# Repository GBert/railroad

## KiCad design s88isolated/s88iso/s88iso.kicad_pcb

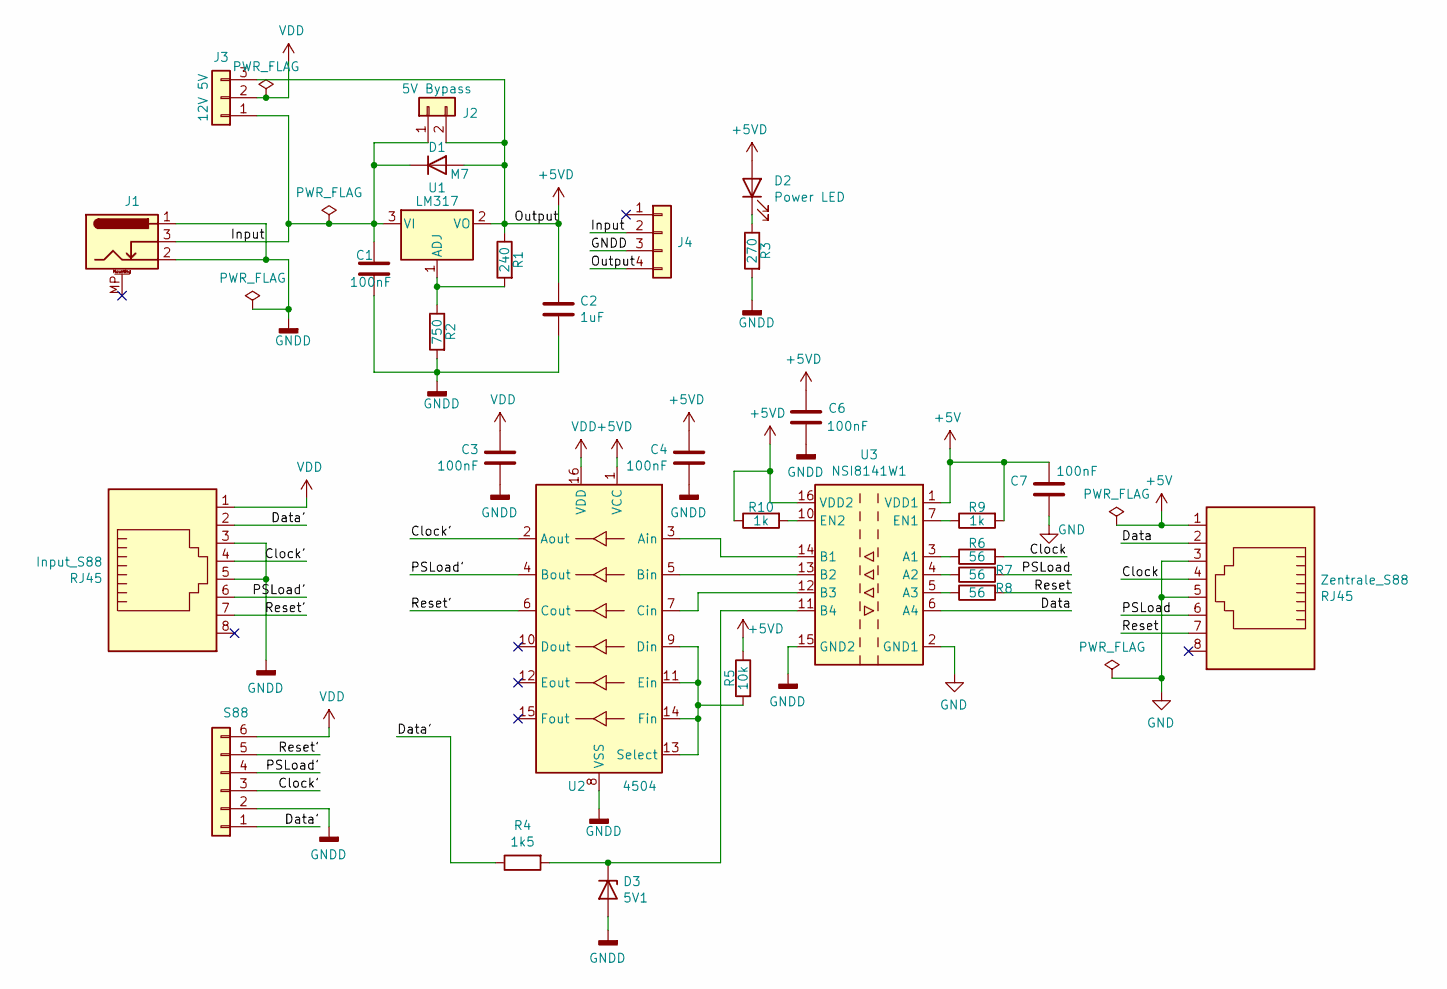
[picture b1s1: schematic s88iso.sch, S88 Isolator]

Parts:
C1, C3, C4, C6, C7: 100nF; C_0805_2012Metric; LCSC C28233
C2: 1uF; C_0805_2012Metric_Pad1.18x1.45mm_HandSolder; LCSC C28323
D1: M7; D_SMA; LCSC C95872
D2: Power LED; LED_0603_1608Metric_Pad1.05x0.95mm_HandSolder; LCSC C72043
D3: 5V1; D_0805_2012Metric_Pad1.15x1.40mm_HandSolder
Input_S88: RJ45; megb8-8-Uni
J1: Barrel_Jack_Switch_MountingPin; dc_socket
J2: 5V Bypass; PinHeader_1x02_P2.54mm_Vertical
J3: 12V 5V; PinHeader_1x03_P2.54mm_Vertical
J4: Conn_01x04; PinSocket_1x04_P2.54mm_Vertical
R1: 240; R_0603_1608Metric_Pad0.98x0.95mm_HandSolder; LCSC C23350
R2: 750; R_0603_1608Metric_Pad0.98x0.95mm_HandSolder; LCSC C23241
R3: 270; R_0603_1608Metric_Pad0.98x0.95mm_HandSolder; LCSC C22966
R4: 1k5; R_0805_2012Metric; LCSC C4310
R5: 10k; R_0805_2012Metric; LCSC C25804
R6, R7, R8: 56; R_0603_1608Metric_Pad0.98x0.95mm_HandSolder; LCSC C25196
R9, R10: 1k; R_0603_1608Metric_Pad0.98x0.95mm_HandSolder; LCSC C21190
S88: Conn_01x06; PinSocket_1x06_P2.54mm_Horizontal
U1: LM317; TO-252-2; LCSC C75510
U2: 4504; SOIC-16_3.9x9.9mm_P1.27mm; LCSC C151885
U3: NSI8141W1; SOIC-16W_7.5x10.3mm_P1.27mm; LCSC C399514
Zentrale_S88: RJ45; megb8-8-Uni

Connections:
+5V: C7.1, R9.2, U3.1 (VDD1), Zentrale_S88.1
/Clock: R6.2, Zentrale_S88.4
/Clock': Input_S88.4, S88.3, U2.2 (Aout)
/Data: U3.6 (A4), Zentrale_S88.2
/Data': Input_S88.2, R4.1, S88.1
/Input: C1.1, D1.1 (K), J1.3, J2.1, J3.1, J4.2, U1.3 (VI)
/PSLoad: R7.2, Zentrale_S88.6
/PSLoad': Input_S88.6, S88.4, U2.4 (Bout)
/Reset: R8.2, Zentrale_S88.7
/Reset': Input_S88.7, S88.5, U2.6 (Cout)
GND: C7.2, U3.2 (GND1), U3.8 (GND1), Zentrale_S88.3, Zentrale_S88.5
GNDD: C1.2, C2.2, C3.2, C4.2, C6.2, D3.2 (A), Input_S88.3, Input_S88.5, J1.1, J1.2, J4.3, R2.2, R3.2, S88.2, U2.8 (VSS), U3.9 (GND2), U3.15 (GND2)
unnamed: D2.1 (K), R3.1
unnamed: D3.1 (K), R4.2, U3.11 (B4)
unnamed: R1.2, R2.1, U1.1 (ADJ)
unnamed: U2.3 (Ain), U3.14 (B1)
unnamed: U2.5 (Bin), U3.13 (B2)
unnamed: U2.7 (Cin), U3.12 (B3)
unnamed: R5.2, U2.9 (Din), U2.11 (Ein), U2.13 (Select), U2.14 (Fin)
unnamed: R6.1, U3.3 (A1)
unnamed: R7.1, U3.4 (A2)
unnamed: R8.1, U3.5 (A3)
unnamed: R9.1, U3.7 (EN1)
unnamed: R10.2, U3.10 (EN2)
VDD: C3.1, Input_S88.1, J3.2, S88.6, U2.16 (VDD)

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
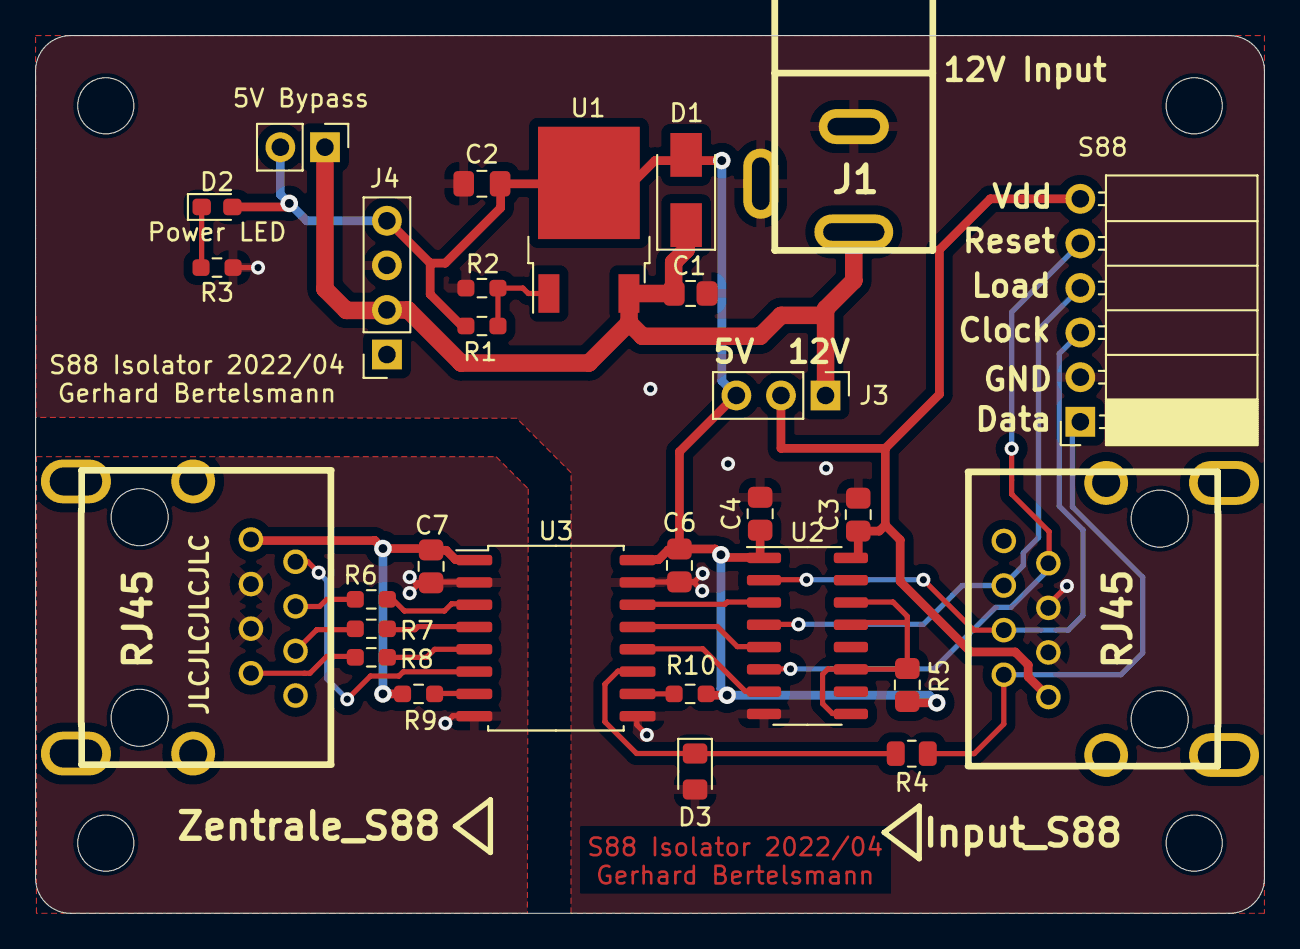
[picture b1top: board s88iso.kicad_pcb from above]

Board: 2 copper layers, 70.0 x 50.0 mm, 29 parts (0 on the bottom side), 27 nets.

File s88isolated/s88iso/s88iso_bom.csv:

Comment,Designator,Footprint,LCSC
"1uF","C2","Capacitor_SMD:C_0805_2012Metric_Pad1.18x1.45mm_HandSolder","C28323"
"100nF","C1,C3,C4,C6,C7","Capacitor_SMD:C_0805_2012Metric","C28233"
"M7","D1","Diode_SMD:D_SMA","C95872"
"Power LED","D2","LED_SMD:LED_0603_1608Metric_Pad1.05x0.95mm_HandSolder","C72043"
"240","R1","Resistor_SMD:R_0603_1608Metric_Pad0.98x0.95mm_HandSolder","C23350"
"750","R2","Resistor_SMD:R_0603_1608Metric_Pad0.98x0.95mm_HandSolder","C23241"
"270","R3","Resistor_SMD:R_0603_1608Metric_Pad0.98x0.95mm_HandSolder","C22966"
"1k5","R4","Resistor_SMD:R_0805_2012Metric","C4310"
"10k","R5","Resistor_SMD:R_0805_2012Metric","C25804"
"56","R6,R7,R8","Resistor_SMD:R_0603_1608Metric_Pad0.98x0.95mm_HandSolder","C25196"
"1k","R9,R10","Resistor_SMD:R_0603_1608Metric_Pad0.98x0.95mm_HandSolder","C21190"
"LM317","U1","Package_TO_SOT_SMD:TO-252-2","C75510"
"4504","U2","Package_SO:SOIC-16_3.9x9.9mm_P1.27mm","C151885"
"NSI8141W1","U3","Package_SO:SOIC-16W_7.5x10.3mm_P1.27mm","C399514"

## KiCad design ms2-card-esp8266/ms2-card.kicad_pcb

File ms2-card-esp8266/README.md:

Lokkarten Emulator
==================

Auf der Lokkarte befindet sich ein I2C EEPROM (24LC64 64kBit -> 8kByte). Die Schaltung
ersetzt den Speicher durch ein kompatiblen FRAM Baustein (U2). Dadurch entfällt die
zeitkritische I2C Slave Behandlung.

Der Prozessor (ESP8266 oder extern) befüllt den FRAM Baustein mit Lokkarten Daten. Damit
es zu keinen Komplikationen auf dem MS2 I2C Bus kommen kann, ist der I2C Bus durch analoge
Schalter (BL1551B - Signal I2C_Select) getrennt.

Der Prozessor signalisiert das Einstecken der Lokkarte (Signal Card) durch Verbindung
der Kontakte am Kartenrand.

Die Platine wurde mit KiCad 7.0.11 erstellt. Die Produktionsdaten wurden mit dem JLCPCB
Fabrication Toolkit Plugin generiert (Verzeichnis production). Platinendicke: 0,8 mm wählen !

Die zwei Fehler im DRC Check (Corteyards overlap) können ignoriert werden, da die Bestückung
mit dem SPI EEPROM U10 und C11 alternativ ist.

Detail-Beschreibung
-------------------

Der Kartenwechsel wird bei der MS2 über einen mechanischen Taster erkannt. Bei der MS2 wurden
verschiedene Arten des Tasters verbaut. Die Platine verwendet einen federnden Testpin, damit
ein Kartenwechsel für die verschiedene Bauarten simuliert werden kann:
https://dirtypcbs.com/store/designer/details/ian/12/dirty-pogo-pins

Power Select: hier wählt man zwiechen Versorgung durch MS2 oder USB.

Schaltregler kann als Ersatz dienen, wenn der Längsregler U6 nicht ausreicht.
Dazu muss U6 aber entfernt werden.

Für C1 ist ein Tantal Kondensator vorgesehen. Da Tantal aber ein Rohstoff aus Krisengebieten
ist, ist ein anderer Kondensator mit niedrigem ESR ratsam. Die Pads sollten genügend Platz bieten,
einen anderen Kondensator einzusetzen, wie z.B. Reichelts "VF 100/6,3 P-C" oder "VF 100/16 P-D".

Silabs CP2102 wurde für die Seriell-USB Anbindung gewählt, weil dieser ein guter Kompromiss
zwischen Stabilität, Unterstützung und Preis ist.

Q1/Q2 und R8/R9 dienen dazu, das Update der ESP8266 ohne Eingriff zu ermöglichen.

U3 und U4 trennen den I2C Bus von der MS2, damit es keine Störungen des MS2 I2C-Busses gibt.
I2C Select schaltet entweder den ESP8266 oder alternativ einen anderen I2C Master
für den Zugriff auf das FRAM hinzu.

U20 dient dazu, einen Kartenwechsel der MS2 zu signalisieren.

Das MS2 I2C Bus Clock Signal wird zusätzlich auch noch über Q1 und ein RC Glied an den ADC
des ESP8266 Moduls angeschlossen, um den Zeitpunkt des letzten I2C Bus Zugriffs zu messen.

TODOs/Done
----------

- CP2102 Test  - OK
- I2C intern Test - OK
- I2C extern Test - OK
- ESP Programmierung Test - OK
- SD Kartenanbindung Test - OK
- Allternative zur SD-Karte - SPI EEPROM - ungetestet

Hardware / neue Version
- 470 nH Vdd

ESP8266 - Code Segmente
-----------------------

```
#define SPI_MISO    12
#define SPI_MOSI    13
#define SPI_CLK     14
#define SPI_CS      15

#define I2C_Select   2
#define I2C_SDA      4
#define I2C_SCL      5
#define Card_Change 16

void setup () {
  // SD Karte initialisieren
  SD.begin(SPI_CS)

  // I2C initilisieren
  Wire.begin(I2C_SDA, I2C_SCL);
  Wire.setClock(100000);

  pinMode(Card_Change, OUTPUT);
  pinMode(I2C_Select, OUTPUT);
}

  // MS2 I2C FRAM Zugriff
  digitalWrite(I2C_Select, 0);
  ...
  // ESP8266 I2C FRAM Zugriff
  digitalWrite(I2C_Select, 1);

  // Kartenwechsel emulieren
  digitalWrite(Card_Change, 0)
  delay(500);
  digitalWrite(Card_Change, 1)

```

Flashing
--------
```
esptool.py --port /dev/ttyUSB1 erase_flash
esptool.py --port /dev/ttyUSB1 --baud 460800 write_flash --flash_size=detect 0 ./build_output/firmware/tasmota.bin
```

OLD - BACKUP
------------

SD-CARD
-------
https://github.com/arendst/Tasmota/discussions/13938

https://www.mikrocontroller.net/articles/MMC-_und_SD-Karten

Raspberry Pi I2C
----------------

|Function  | GPIO   | Pin    |      |
|----------|--------|--------|------|
|SDA       | GPIO2  | Pin 3  |      |
|SCL       | GPIO3  | Pin 5  |      |

Tasmota Tests
-------------

git clone https://github.com/arendst/Tasmota.git
cd Tasmota
git tag
pio run

{"NAME":"ESP-12F","GPIO":[1,1,1,1,1,1,0,0,1,1,1,1,1,1],"FLAG":0,"BASE":18}

user_config_override.h
```
// Select none or only one of the below defines USE_RULES or USE_SCRIPT
#ifdef USE_RULES 
#undef USE_RULES                                // Add support for rules (+8k code)
#endif

#ifndef USE_SCRIPT
#define USE_SCRIPT
#endif
#define SDCARD_DIR //Not essential I think
#define USE_SCRIPT_FATFS_EXT //Not essential I think
#define USE_SCRIPT_FATFS //Not essential I think
#define USE_UFILESYS
#define USE_SDCARD
#define SDCARD_CS_PIN 4 //Not strictly necessary since the same #define happens in xdrv_50_filesystem.ino

//Further down I define SPI

#define USE_SPI
```

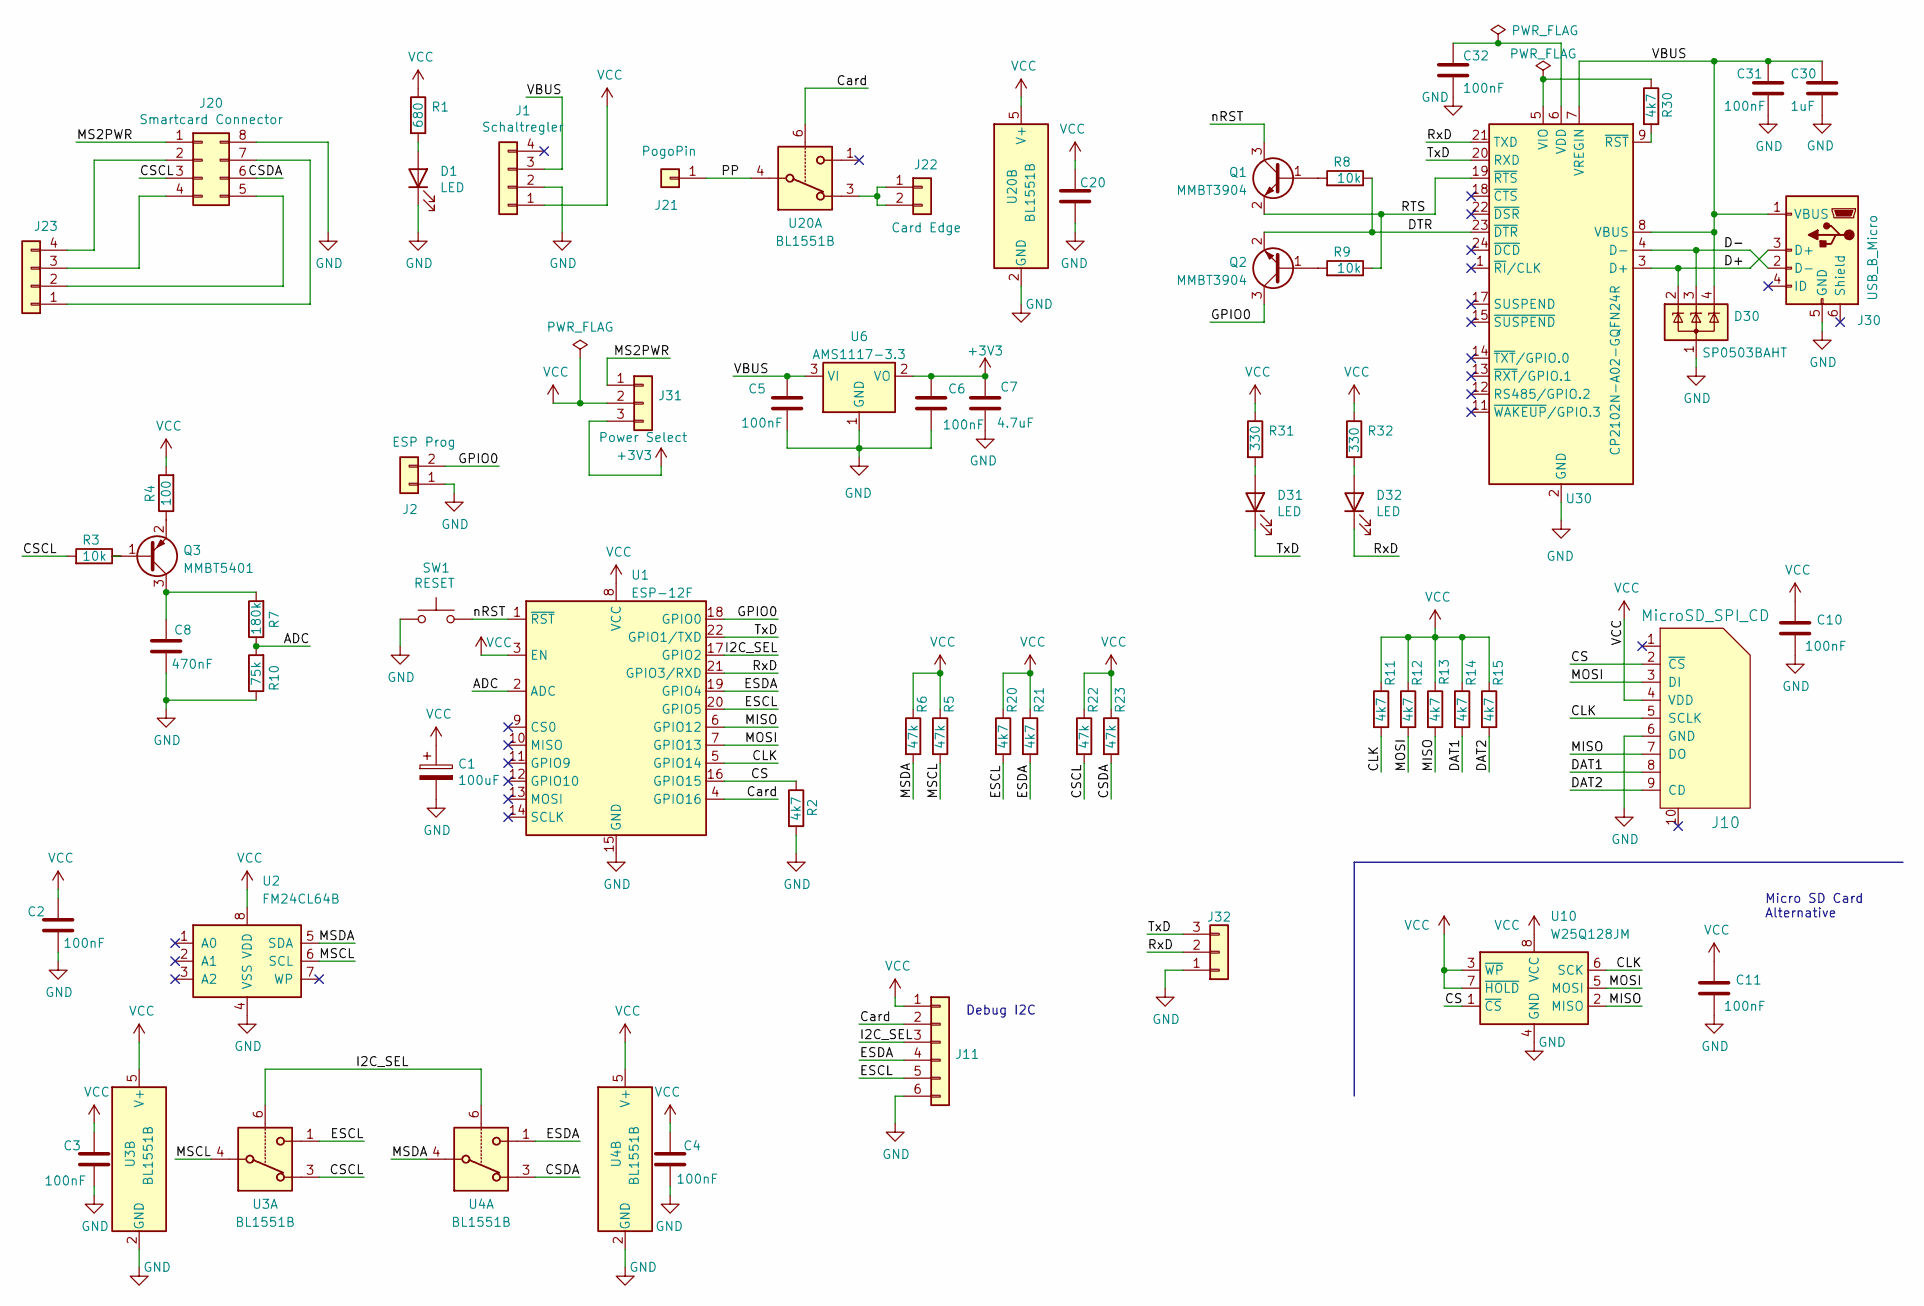
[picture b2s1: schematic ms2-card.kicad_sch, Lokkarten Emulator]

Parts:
C1: 100uF; CP_EIA-7343-31_Kemet-D_Pad2.25x2.55mm_HandSolder
C2, C3, C4, C5, C6, C10, C11, C20, C31, C32: 100nF; C_0603_1608Metric; LCSC C14663
C7: 4.7uF; C_0805_2012Metric; LCSC C1779
C8: 470nF; C_0603_1608Metric; LCSC C1623
C30: 1uF; C_0805_2012Metric; LCSC C28323
D1, D31, D32: LED; LED_0603_1608Metric; LCSC C2286
D30: SP0503BAHT; SOT-143; LCSC C3040626
J1: Schaltregler; PinHeader_1x04_P2.54mm_Vertical
J2: ESP Prog; PinHeader_1x02_P2.54mm_Vertical
J10: MicroSD_SPI_CD; GCT-MEM2055-00-190-01-A; LCSC C2889258
J11: Conn_01x06; PinHeader_1x06_P2.54mm_Vertical
J20: Smartcard Connector; iso7816_conn
J21: PogoPin; PogoPin2
J22: Card Edge; MS2_Edge
J23: Conn_01x04; PinHeader_1x04_P1.27mm_Vertical
J30: USB_B_Micro; USB_Micro-B_Amphenol_10118194_Horizontal; LCSC C132563
J31: Power Select; PinHeader_1x03_P2.54mm_Vertical
J32: Conn_01x03; PinHeader_1x03_P2.54mm_Vertical
Q1, Q2: MMBT3904; SOT-23; LCSC C20526
Q3: MMBT5401; SOT-23; LCSC C8326
R1: 680; R_0603_1608Metric; LCSC C23228
R2, R11, R12, R13, R14, R15, R20, R21, R30: 4k7; R_0603_1608Metric; LCSC C23162
R3, R8, R9: 10k; R_0603_1608Metric; LCSC C25804
R4: 100; R_0603_1608Metric; LCSC C22775
R5, R6, R22, R23: 47k; R_0603_1608Metric; LCSC C25819
R7: 180k; R_0603_1608Metric; LCSC C22827
R10: 75k; R_0603_1608Metric; LCSC C23242
R31, R32: 330; R_0603_1608Metric; LCSC C23138
SW1: RESET; SW_PUSH_6mm_H4.3mm
U1: ESP-12F; ESP-12E; LCSC C82891
U2: FM24CL64B; SOIC-8_3.9x4.9mm_P1.27mm; LCSC C9829
U3, U4, U20: BL1551B; SOT-363_SC-70-6; LCSC C2944066
U6: AMS1117-3.3; SOT-223-3_TabPin2; LCSC C6186
U10: W25Q128JM; SOIC-8_3.9x4.9mm_P1.27mm
U30: CP2102N-A02-GQFN24R; QFN-24-1EP_4x4mm_P0.5mm_EP2.6x2.6mm; LCSC C969151

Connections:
+3V3: C6.1, C7.1, J31.3, U6.2 (VO)
/ADC: R7.1, R10.2, U1.2 (ADC)
/CLK: J10.5 (SCLK), R11.2, U1.5 (GPIO14), U10.6 (SCK)
/CS: J10.2 (~CS), R2.1, U1.16 (GPIO15), U10.1 (~CS)
/CSCL: J20.3, R3.2, R22.2, U3.3
/CSDA: J20.6, R23.2, U4.3
/Card: J11.2, U1.4 (GPIO16), U20.6
/D+: D30.2 (K), J30.3 (D+), U30.3 (D+)
/D-: D30.3 (K), J30.2 (D-), U30.4 (D-)
/DAT1: J10.8, R14.2
/DAT2: J10.9 (CD), R15.2
/DTR: Q2.2 (E), R8.1, U30.23 (~DTR)
/ESCL: J11.5, R20.2, U1.20 (GPIO5), U3.1
/ESDA: J11.4, R21.2, U1.19 (GPIO4), U4.1
/GPIO0: J2.2, Q2.3 (C), U1.18 (GPIO0)
/I2C_SEL: J11.3, U1.17 (GPIO2), U3.6, U4.6
/MISO: J10.7 (DO), R13.2, U1.6 (GPIO12), U10.2 (MISO)
/MOSI: J10.3 (DI), R12.2, U1.7 (GPIO13), U10.5 (MOSI)
/MS2PWR: J20.1, J31.1
/MSCL: R5.2, U2.6 (SCL), U3.4
/MSDA: R6.2, U2.5 (SDA), U4.4
/PP: J21.1, U20.4
/RTS: Q1.2 (E), R9.1, U30.19 (~RTS)
/RxD: D32.1 (K), J32.2, U1.21 (GPIO3/RXD), U30.21 (TXD)
/TxD: D31.1 (K), J32.3, U1.22 (GPIO1/TXD), U30.20 (RXD)
/VBUS: C5.1, C30.1, C31.1, D30.4 (K), J1.3, J30.1 (VBUS), U6.3 (VI), U30.7 (VREGIN), U30.8 (VBUS)
/nRST: Q1.3 (C), SW1.2, U1.1 (~RST)
GND: C1.2, C2.2, C3.2, C4.2, C5.2, C6.2, C7.2, C8.2, C10.2, C11.2, C20.2, C30.2, C31.2, C32.2, D1.1 (K), D30.1 (A), J1.2, J2.1, J10.6 (GND), J11.6, J20.8, J30.5 (GND), J32.1, R2.2, R10.1, SW1.1, U1.15 (GND), U2.4 (VSS), U3.2 (GND), U4.2 (GND), U6.1 (GND), U10.4 (GND), U20.2 (GND), U30.2 (GND), U30.25 (GND)
unnamed: D1.2 (A), R1.2
unnamed: D31.2 (A), R31.2
unnamed: D32.2 (A), R32.2
unnamed: J20.2, J23.4
unnamed: J20.4, J23.3
unnamed: J20.5, J23.2
unnamed: J20.7, J23.1
unnamed: J22.1, J22.2, U20.3
unnamed: Q1.1 (B), R8.2
unnamed: Q2.1 (B), R9.2
unnamed: Q3.1 (B), R3.1
unnamed: C8.1, Q3.3 (C), R7.2
unnamed: Q3.2 (E), R4.1
unnamed: C32.1, U30.6 (VDD)
unnamed: R30.1, U30.5 (VIO)
unnamed: R30.2, U30.9 (~RST)
VCC: C1.1, C2.1, C3.1, C4.1, C10.1, C11.1, C20.1, J1.1, J10.4 (VDD), J11.1, J31.2, R1.1, R4.2, R5.1, R6.1, R11.1, R12.1, R13.1, R14.1, R15.1, R20.1, R21.1, R22.1, R23.1, R31.1, R32.1, U1.3 (EN), U1.8 (VCC), U2.8 (VDD), U3.5 (V+), U4.5 (V+), U10.3 (~WP), U10.7 (~HOLD), U10.8 (VCC), U20.5 (V+)

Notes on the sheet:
Debug I2C
Micro SD Card Alternative

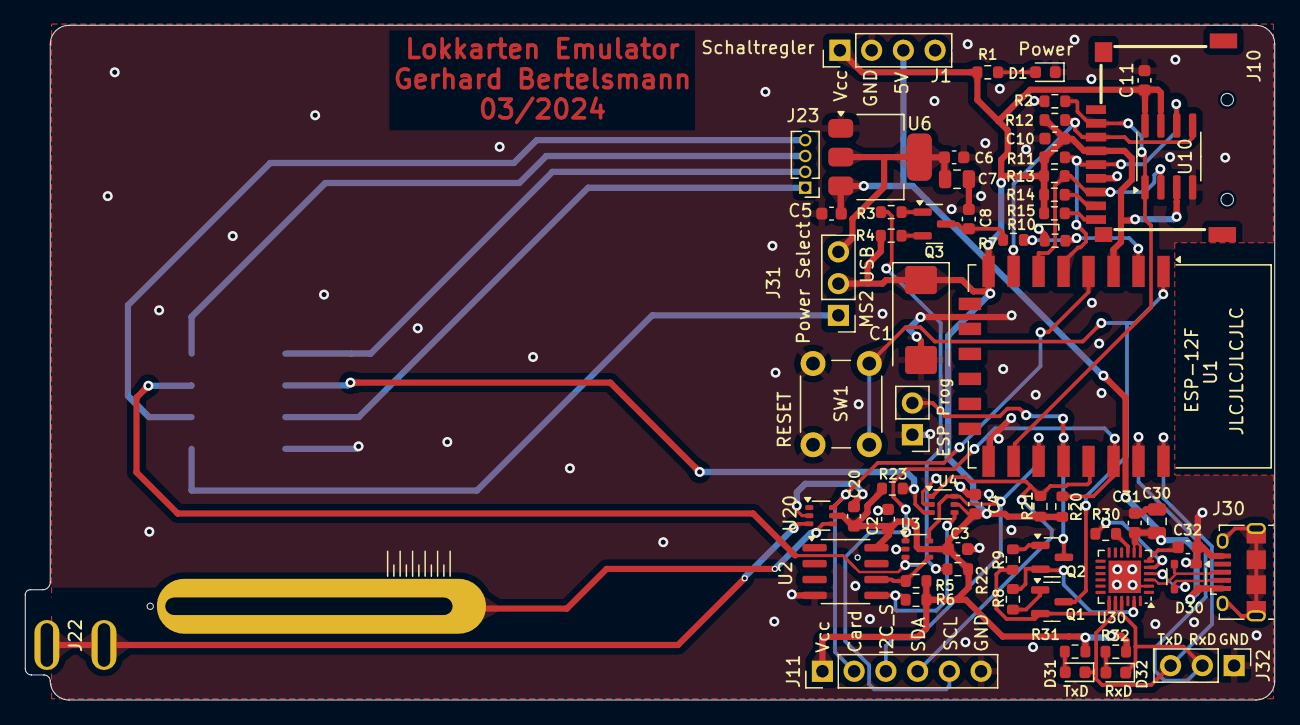
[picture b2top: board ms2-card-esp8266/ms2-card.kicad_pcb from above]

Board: 2 copper layers, 100.0 x 54.0 mm, 63 parts (1 on the bottom side), 45 nets.

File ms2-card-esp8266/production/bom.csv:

Designator,Footprint,Quantity,Value,LCSC Part #
"C10, C2, C20, C3, C31, C32, C4, C5, C6",0603,9,100nF,C14663
C30,0805,1,1uF,C28323
C7,0805,1,4.7uF,C1779
C8,0603,1,470nF,C1623
"D1, D31, D32",0603,3,LED,C2286
D30,SOT-143,1,SP0503BAHT,C3040626
J10,GCT-MEM2055-00-190-01-A,1,MicroSD_SPI_CD,C2889258
J30,USB_Micro-B_Amphenol_10118194_Horizontal,1,USB_B_Micro,C132563
"Q1, Q2",SOT-23,2,MMBT3904,C20526
Q3,SOT-23,1,MMBT5401,C8326
R1,0603,1,680,C23228
R10,0603,1,75k,C23242
"R11, R12, R13, R14, R15, R2, R20, R21, R30",0603,9,4k7,C23162
"R22, R23, R5, R6",0603,4,47k,C25819
"R3, R8, R9",0603,3,10k,C25804
"R31, R32",0603,2,330,C23138
R4,0603,1,100,C22775
R7,0603,1,180k,C22827
U1,ESP-12E,1,ESP-12F,C82891
U2,SOIC-8_3.9x4.9mm_P1.27mm,1,FM24CL64B,C9829
"U20, U3, U4",SOT-363_SC-70-6,3,BL1551B,C2944066
U30,QFN-24-1EP_4x4mm_P0.5mm_EP2.6x2.6mm,1,CP2102N-A02-GQFN24R ,C969151
U6,SOT-223-3_TabPin2,1,AMS1117-3.3,C6186

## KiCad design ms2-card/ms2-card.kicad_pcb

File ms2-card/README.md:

ESP8266
-------

Tasmota Tests
-------------

git clone https://github.com/arendst/Tasmota.git
cd Tasmota
git tag
pio run

{"NAME":"ESP-12F","GPIO":[1,1,1,1,1,1,0,0,1,1,1,1,1,1],"FLAG":0,"BASE":18}

user_config_override.h
```
// Select none or only one of the below defines USE_RULES or USE_SCRIPT
#ifdef USE_RULES 
#undef USE_RULES                                // Add support for rules (+8k code)
#endif

#ifndef USE_SCRIPT
#define USE_SCRIPT
#endif
#define SDCARD_DIR //Not essential I think
#define USE_SCRIPT_FATFS_EXT //Not essential I think
#define USE_SCRIPT_FATFS //Not essential I think
#define USE_UFILESYS
#define USE_SDCARD
#define SDCARD_CS_PIN 4 //Not strictly necessary since the same #define happens in xdrv_50_filesystem.ino

//Further down I define SPI

#define USE_SPI
```

Flashing
--------
```
esptool.py --port /dev/ttyUSB1 erase_flash 
esptool.py --port /dev/ttyUSB1 --baud 460800 write_flash --flash_size=detect 0 ./build_output/firmware/tasmota.bin
```

Raspberry Pi I2C Slave
----------------------

|Function  | GPIO   | Pin    |      |
|----------|--------|--------|------|
|SDA       | GPIO2  | Pin 3  |      |
|SCL       | GPIO3  | Pin 5  |      |
|SDA Slave | GPIO10 | Pin 19 | used |
|SCL Slave | GPIO11 | Pin 23 | used |

PI Pico
------------------------------------

I2C Slave

| GPIO | Function |       |
|------|----------|-------|
| GP4  | SDA      | PIN 6 |
| GP5  | SCL      | PIN 7 |

https://draeger-it.blog/maker-pi-pico-2-sensordaten-auf-einer-sd-card-speichern/

| GPIO   | SD Mode | SPI Mode   |
|--------|---------|------------|
| GP10   | CLK     | SCK        |
| GP11   | CMD     | SDI / MOSI |
| GP12   | DAT0	   | SDO / MISO |
| GP13   | DAT1	   | X          |
| GP14   | DAT2	   | X          |
| GP15   | CD/DAT3 | CSn        |

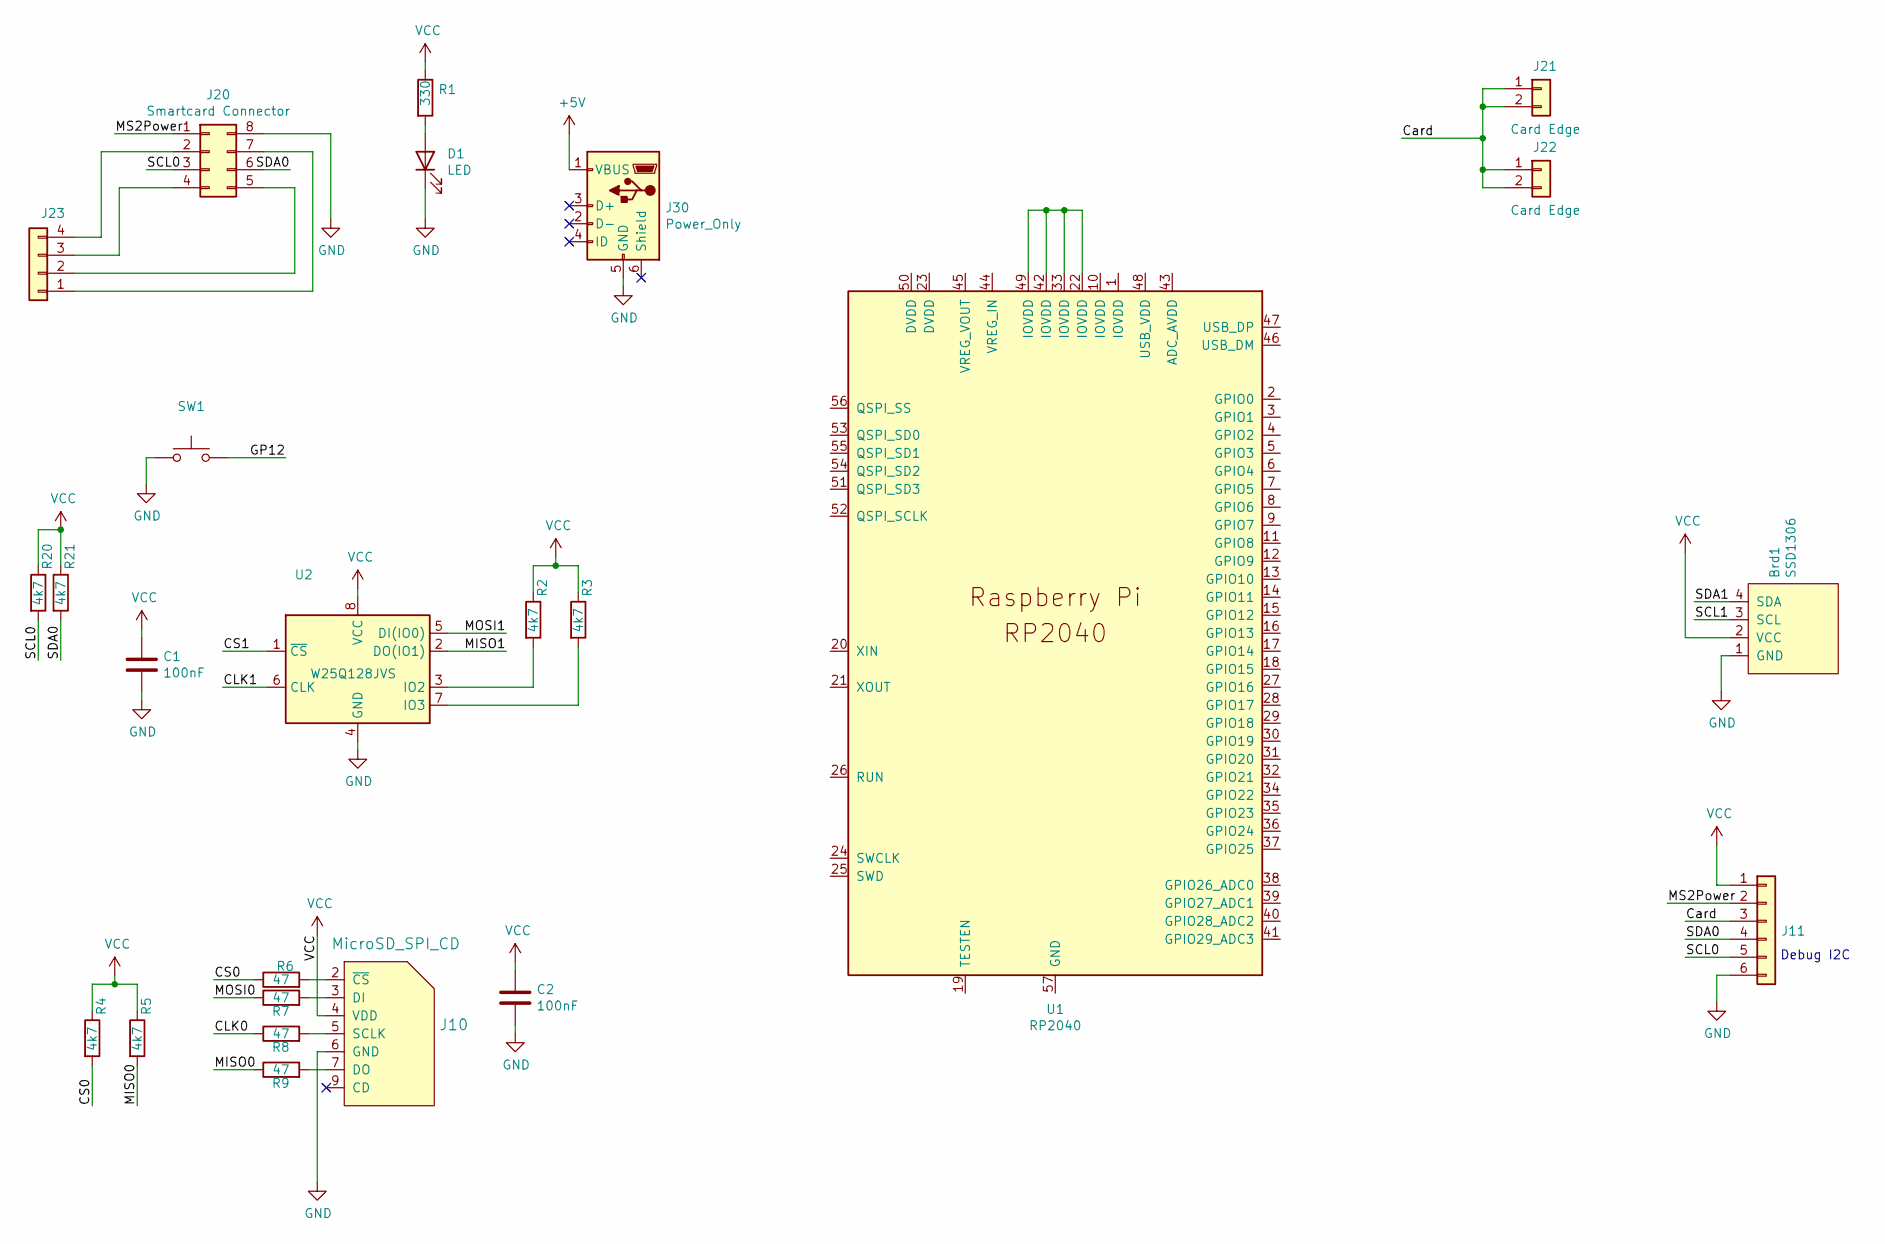
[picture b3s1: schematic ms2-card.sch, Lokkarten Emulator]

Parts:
Brd1: SSD1306; 128x64OLED
C1, C2: 100nF; C_0805_2012Metric_Pad1.18x1.45mm_HandSolder
D1: LED; LED_0805_2012Metric_Pad1.15x1.40mm_HandSolder
J10: MicroSD_SPI_CD; GCT-MEM2055-00-190-01-A
J11: Conn_01x06; PinHeader_1x06_P2.54mm_Vertical
J20: Smartcard Connector; iso7816_conn
J21, J22: Card Edge; MS2_Edge
J23: Conn_01x04; PinHeader_1x04_P1.27mm_Vertical
J30: Power_Only; USB_Micro-B_Molex-105017-0001
R1: 330; R_0805_HandSolderingII
R2, R3, R4, R5, R20, R21: 4k7; R_0805_HandSolderingII
R6, R7: 47; R_0603_1608Metric_Pad0.98x0.95mm_HandSolder
R8, R9: 47; R_0805_HandSolderingII
SW1: SW_Push; PCB_PUSH
U1: RP2040; RP2040-QFN-56; JLCPCB C2040
U2: W25Q128JVS; SOIC-8_5.23x5.23mm_P1.27mm; JLCPCB C97521

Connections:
+5V: J30.1 (VBUS)
/CLK0: R8.1
/CLK1: U2.6 (CLK)
/CS0: R4.2, R6.1
/CS1: U2.1 (~CS)
/Card: J11.3, J21.1, J21.2, J22.1, J22.2; also elsewhere on the board
/GP12: SW1.2
/MISO0: R5.2, R9.1
/MISO1: U2.2 (DO(IO1))
/MOSI0: R7.1
/MOSI1: U2.5 (DI(IO0))
/MS2Power: J11.2, J20.1
/SCL0: J11.5, J20.3, R20.2
/SCL1: Brd1.3 (SCL)
/SDA0: J11.4, J20.6, R21.2
/SDA1: Brd1.4 (SDA)
GND: Brd1.1 (GND), C1.2, C2.2, D1.1 (K), J10.6 (GND), J11.6, J20.8, J30.5 (GND), SW1.1, U2.4 (GND)
unnamed: D1.2 (A), R1.2
unnamed: J10.2 (~CS), R6.2
unnamed: J10.3 (DI), R7.2
unnamed: J10.5 (SCLK), R8.2
unnamed: J10.7 (DO), R9.2
unnamed: J20.2, J23.4
unnamed: J20.4, J23.3
unnamed: J20.5, J23.2
unnamed: J20.7, J23.1
unnamed: R2.2, U2.3 (IO2)
unnamed: R3.2, U2.7 (IO3)
unnamed: U1.22 (IOVDD), U1.33 (IOVDD), U1.42 (IOVDD), U1.49 (IOVDD)
VCC: Brd1.2 (VCC), C1.1, C2.1, J10.4 (VDD), J11.1, R1.1, R2.1, R3.1, R4.1, R5.1, R20.1, R21.1, U2.8 (VCC)

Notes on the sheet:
Debug I2C

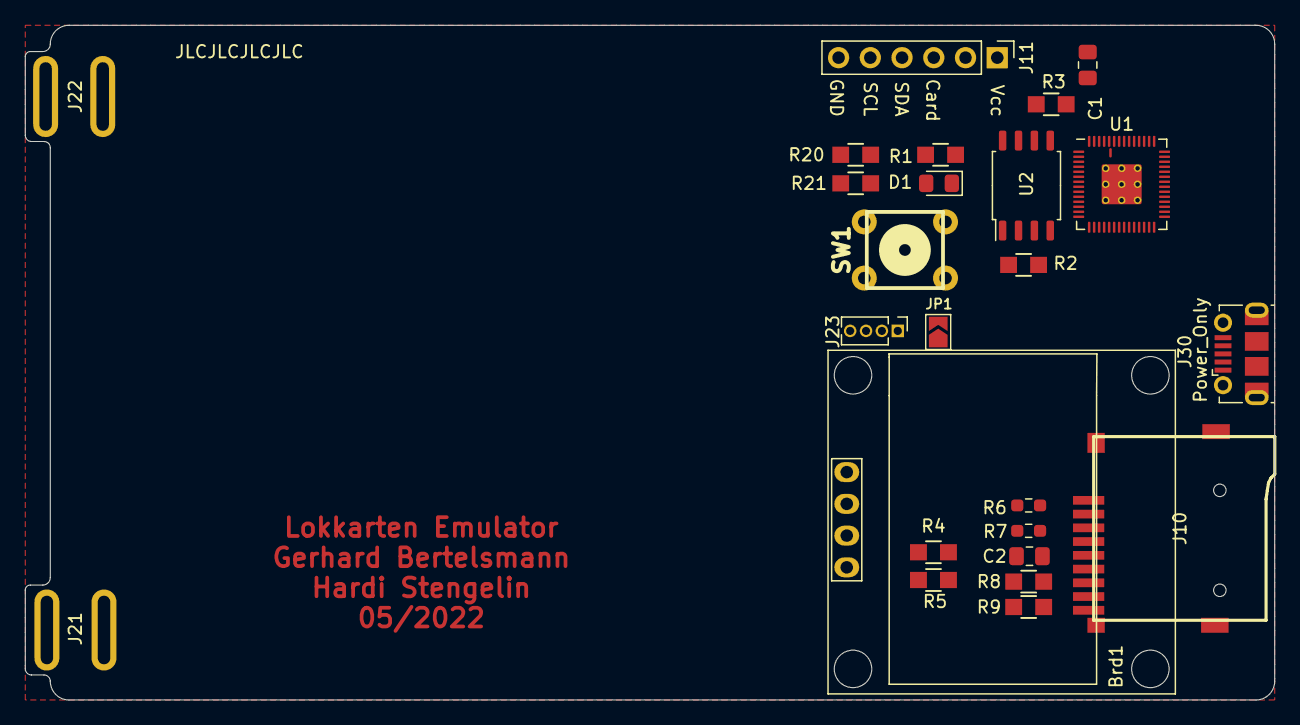
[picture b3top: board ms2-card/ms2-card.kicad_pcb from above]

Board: 2 copper layers, 100.0 x 54.0 mm, 26 parts (1 on the bottom side), 20 nets.

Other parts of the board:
JP1: Jumper; SolderJumper-2_P1.3mm_Open_TrianglePad1.0x1.5mm

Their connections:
/Card: JP1.2; also elsewhere on the board

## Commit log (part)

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2023-04-30 indent
2023-04-30 prepare interface search
2023-05-03 fix IP client address handling
2023-05-03 sizeof is an operator - not a function
2023-05-04 thx to Ralf Mende - "PRAGMA user_version = 15" makes the functions work
2023-05-04 fix date
2023-05-04 fix typo
2023-05-04 uses new uid mapping for locos
2023-05-05 lindent and change button if duration is set
2023-05-05 ignore self send data
2023-05-05 avoid double free
2023-05-06 increase version number for testing by user
2023-05-06 new MS2 type
2023-05-06 be more specific regarding S88 equipment
2023-05-06 typ is unit16_t
2023-05-06 use german
2023-05-09 use tenary operator with less characters
2023-05-09 reuse code and remove boiler plate code
2023-05-09 more cleanup
2023-05-10 allow getting data via http - curl has whitespace problem
2023-05-10 url encoding added
2023-05-11 optimize curl a little bit
2023-05-14 move config_data to a seperate struct
2023-05-14 fix memory leak
2023-05-15 find the IP address for the Z21 database
2023-05-15 indenting
2023-05-15 incremt version number
2023-05-15 use deep link for lokomotive.cs2
2023-05-15 use different default interface list
2023-05-15 need to set fullpath using minizip
2023-05-15 minizip like it this way
2023-05-15 fix help
2023-05-16 add missing usage text
2023-05-16 using switch -v for verbose output
2023-05-16 keep this compiling
2023-05-16 use verbos print also here - if there is no loco stop program
2023-05-16 make a new version
2023-05-16 update usage
2023-05-25 add WR902AC can2lan init
2023-05-26 add TL-WR902AC-v3 virtual can init
2023-05-26 copy correct init file
2023-05-28 new version from Teddy
2023-05-28 add missing files
2023-05-28 prepare automatic mode
2023-05-29 close UDP sockets here
2023-05-29 using -a swith to find CS2 ip and use it to get all the data from the device
2023-05-29 using some UDP funtions from net.c
2023-05-29 prepare -a switch
2023-05-29 use the fancy setup_udp_socket function so save some lines of code
2023-05-29 this is the secondary port when fail
2023-05-31 integrate empty Database into program
2023-06-11 fix programm
2023-06-12 fix filesize - hopefully
2023-06-15 fix warning
2023-06-15 fix bug - hopefully
2023-06-15 fix compiler warning
2023-06-15 use new version number
2023-06-16 indent and add some hints
2023-07-06 set full embedded CAN/UDP frame to zero as suggested by Rainer Mueller
2023-07-07 do local if can2udp ist startet for MaeCAN as suggested by Rainer Mueller
2023-08-05 new version from Rainer Mueller
2023-08-08 fix default config dir
2023-08-09 add Rainers cahnges including basic Z21 debug / prepare splitting code
2023-08-09 fix Z21 packet handling
2023-08-09 change output a little bit
2023-08-09 start splitting code
2023-08-09 split the code
2023-08-09 don't need can/raw.h everywhere
2023-08-09 more splitting
2023-08-10 Makefile looks better
2023-08-10 more splitting ...
2023-08-10 missing makefile
2023-08-10 add gitignore
2023-08-11 add decompressing config data
2023-08-11 move another function to the specific decoder source
2023-08-11 reuse more code
2023-08-11 use same output for Z21 conf
2023-08-11 thats a little bit shorter
2023-08-11 add observed CS2 GUI identifier
2023-08-11 alloc buffer for config stream
2023-08-11 free zlib buffer
2023-08-11 close pcap handle to calm valgrind
2023-08-11 don't alloc twice - we do it in the inflation function
2023-08-11 move function to CS2 decoder
2023-08-11 move it to CS2 decoder
2023-08-11 Lindent
2023-08-13 fix memcmp as suggested by Rainer
2023-08-13 fix comment
2023-08-13 use original timestamp
2023-08-13 move CS2 channel code to decoder file
2023-08-13 omit test data
2023-08-16 deocde measurement values - wip
2023-08-16 deocde measurement - looks better
2023-08-16 tidy it and increase version number
2023-08-16 fix path
2023-08-16 save changes
2023-08-16 fix mkdir option
2023-08-23 reflect source change
2023-08-23 fix UDP handling (LodiCon)
2023-09-07 take can-monitor as seperate package
2023-09-07 fix Makefile
2023-09-07 fix Makefile - part II
2023-09-07 fix Makefile - part III
2023-09-07 fix alloc warning
2023-09-07 add .gitignore
2023-09-07 housekeeping
2023-09-07 use default channel definitions for Gleisbox
2023-09-07 don't git vim swap fileswq
2023-09-07 one digit is enough
2023-09-07 only print hex measurement value if definition is unknown
2023-09-07 make minor new version
2023-09-07 precise hint
2023-09-07 sounds better
2023-09-07 add copy command
2023-09-08 print Kanal decimal instead of hex
2023-09-15 play safe
2023-09-24 add missing sources
2023-09-24 only print if verbose mode set
2023-09-26 Rainers zero point fix
2023-09-26 check if buffer is available
2023-09-26 add space in output
2023-09-26 that needs to be checked
2023-09-26 calm down some compilers / hint by Rainer
2023-09-26 fixes by Rainer
2023-10-11 calm down Visual Studio Compiler as suggested by Rainer
2023-10-22 fix memory leak by Rainer
2023-11-06 change UDP ports to standard and do no longer use can2udp for special ports
2023-11-15 fix by Teddy
2023-12-20 fix -t 0 (only once) feature
2023-12-20 use new version for updating
2023-12-20 don't do fixes on a rush
2024-01-14 fix magnet handling
2024-01-14 fix turnout handling and add default decoder type setting
2024-01-14 fix address handling hint
2024-01-14 avoid reading magnets if default turnout decoder type is set
2024-02-19 FRAM and ESP8266
2024-02-19 in production
2024-02-19 first production
2024-02-20 replace SW1 / calm down DRC - part I
2024-02-21 it is 23 decided by Teddy
2024-02-21 fix SD CARD DRC check
2024-02-21 add basic description and actual drawing
2024-02-21 add some todos
2024-02-22 fix issues regarding power supply - thanks MK
2024-02-22 minor changes
2024-02-22 Teddys fix for sqlite cleanup
2024-02-23 add ADC simulation
2024-02-24 add 3D pic
2024-02-25 use JLCPCB standard parts
2024-02-25 add RC ADC oart
2024-02-25 some small fixes
2024-02-25 pull up unused SD card IO pins
2024-02-25 use wider wires for card connnects
2024-02-26 add actual schematic pdf
2024-02-27 move JLC order number behind SD card
2024-03-02 add SPI EEPROM alternative
2024-03-02 small changes around CP2102
2024-03-02 add JLCPCB position fixes, except J10
2024-03-03 use latest 4.2 JLC production plugin to solve J10 paling issue
2024-03-03 add 3D Model for SPI EEPROM alternative
2024-03-03 switch to KiCad 7 - wip
2024-03-04 elimate errors sourced by KiCad update
2024-03-04 fix rotation / most are done by JLCPCB Fabrication Plugin
2024-03-04 fix error messages
2024-03-05 fix production offset
2024-03-05 fix more DRC issues
2024-03-05 fix ESP-12F offset
2024-03-06 use modified PogoPin footprint for easier production
2024-03-06 update README and add JLCPCB production files
2024-03-06 uodate 3D pictures
2024-03-06 exclude PogoPin footprint from posioning file
2024-03-06 use standard Maerklin ports for Maecan-Server
2024-03-06 change Makefiles to reflect changes
2024-03-07 get rid off some compiler warnings
2024-03-11 print Device ID also in decimal
2024-03-12 send stop signal before shutdown as suggested by Rainer
2024-03-12 fix string handling as suggested by Rainer
2024-03-12 improve reading lococard as suggested by Rainer
2024-03-12 increment packet version for updates
2024-03-13 fix USB D+/D- swap
2024-03-13 move edge connector a little bit
2024-03-16 make power LED a little bit less brighter
2024-03-16 add Tasmota test image including Config
2024-03-16 new pictures of upcoming version
2024-03-17 make power LED less brighter
2024-03-17 add production files
2024-03-17 use teardrops
2024-03-17 fix markings
2024-04-02 add quick Tasmota test config
2024-04-05 update to KiCad 7.0 - wip
2024-04-10 add some pogopin pictures
2024-04-21 this is version 1.0
2024-04-22 add VSCode testing
2024-04-24 more testing
2024-04-25 add pogopin pictures
2024-05-15 avoid crash if LocoCards doesn't exists
2024-05-25 fix memeory issue
2024-05-28 use le16
2024-06-02 more Z21 decoding by Rainer
2024-06-02 fix memory leak as suggested by Rainer
2024-06-11 add basic test firmware
2024-06-14 add more hints
2024-06-14 fix hint
2024-06-14 move SD card hint
2024-06-14 fix compiling
2024-06-14 fix compiling - part II
2024-06-15 adapt to Maxi's version 2021-01-25.1
2024-06-15 updates done within the last three years
2024-06-18 use actual board 3D view
2024-06-18 more detailed view
2024-06-20 add Ubuntu compiling hint
2024-06-20 add Z21 App hint
2024-06-24 synch with Rainer
2024-06-24 set excecute bit
2024-06-24 increase version number
2024-06-30 update Makefile and add config file save
2024-07-29 add more z21 decoding contributed by Rainer
2024-07-29 increment version number
2024-10-06 added functionality to wake-up-links88: provide identifiers of L88 on request
2024-10-06 add specfic LinkS88 setup
2024-10-06 change version number
2024-10-13 add S88 parameters (partly)
2024-10-13 move S88 routine to CS2 decoder file
2024-10-19 add simple PC/SC based lococard reader
2024-10-21 fix receiver buffer copy bug
2024-11-13 Helloween special: fix ghost text by Rainer
2024-11-13 increase version numer for updates
2024-11-25 add support of "lokliste" format
2024-11-27 add Rainers changes for MS2 Slave upload
2025-01-08 change schematic to grid and LED JLCPCB
2025-01-08 missing files
2025-04-03 add missing clock
2025-04-17 only trigger on function set like Rainer suggested
2025-07-09 fix by Rainer for loco cards below 300 bytes
2025-07-11 fix by Rainer
2025-08-03 change timing for protocol and version request, and do cleaning
2025-09-08 new Version from Rainer
2025-10-05 change timing for protocol and version request and do some cleanup
2025-10-07 Reused loop index i in nested loops caused skipping of later TCP clients. Fixed by using a separate inner index j.
    Context: In can2lan.c, the server loops over all active TCP clients with for (i = 0; i <= max_tcp_i; i++).
    Bug: Inside that loop, another loop reused the same variable i to iterate over multiple 13-byte CAN frames inside a single TCP packet.
    Effect: The outer client loop index was advanced by the inner loop, causing remaining clients to be skipped in that iteration (lost/late forwarding, irregular behavior).
    Trigger: Any TCP packet containing one or more CAN frames (even a single 13-byte frame) corrupted the outer loop’s progression.
    Root cause: Variable reuse (loop index c
2025-10-22 use CFLAGS
2025-10-22 add fallthrough hint
2025-10-22 add more fallthrough hints
2025-10-23 add Mobile Station Web App from Ralf Mende
2025-10-24 try to add everthing necessary
2025-10-24 fix init
2025-10-24 fix init - set bin
2025-10-24 fix init - don't use init as extension
2025-10-24 add www dirs and files
2025-10-24 fix templates dir
2025-10-27 test Makefile subdirs
2025-11-08 replace deprecated buffer initialisations
2025-12-08 new Version from Ralf Mende
2026-01-02 change hash for testing
2026-01-03 auto set MS2 version
2026-01-03 fix sentence
2026-01-03 get the MS2 version after plugging it in
2026-01-03 add hint if lokomotive.cs2 is missing Lokliste with MM 1
2026-01-06 new version from Ralf
2026-01-06 increas version number
2026-01-07 keep Maerklin config files
2026-01-10 avoid sqlite update checking
2026-01-10 avoid sqlite update checking- fix
2026-01-19 add fallthrough hints
2026-01-22 fix compiling error
2026-02-10 First Version that reads something from V1.83
2026-02-10 Fix skipping spaces
2026-02-12 Code Cleanup
2026-02-12 Update other methods
2026-02-12 MOve changes to correct file
2026-02-18 let UDP socket share the receive port to allow cooperation
2026-02-19 increase version number to fix Update
2026-02-21 new version fom Teddy
2026-02-27 start creating docker for compiling SRSEII
2026-02-27 add links to files
2026-02-27 add link to org
2026-02-27 fix dir entry
2026-03-02 fix some issues
2026-03-06 Add devcontainer for SRSEII SDK
    Adds a devcontainer containing the SDK for SRSEII. This includes the
    cross compiler for compiling individual binaries as well as all the
    infrastructure needed to produce *.ipk packages.
    The SDK is set up to accomodate the local working copy of the "railroad" repository as a feed.
2026-03-13 add nodejs hint
2026-05-01 clarifications for read/write config and event report selection
